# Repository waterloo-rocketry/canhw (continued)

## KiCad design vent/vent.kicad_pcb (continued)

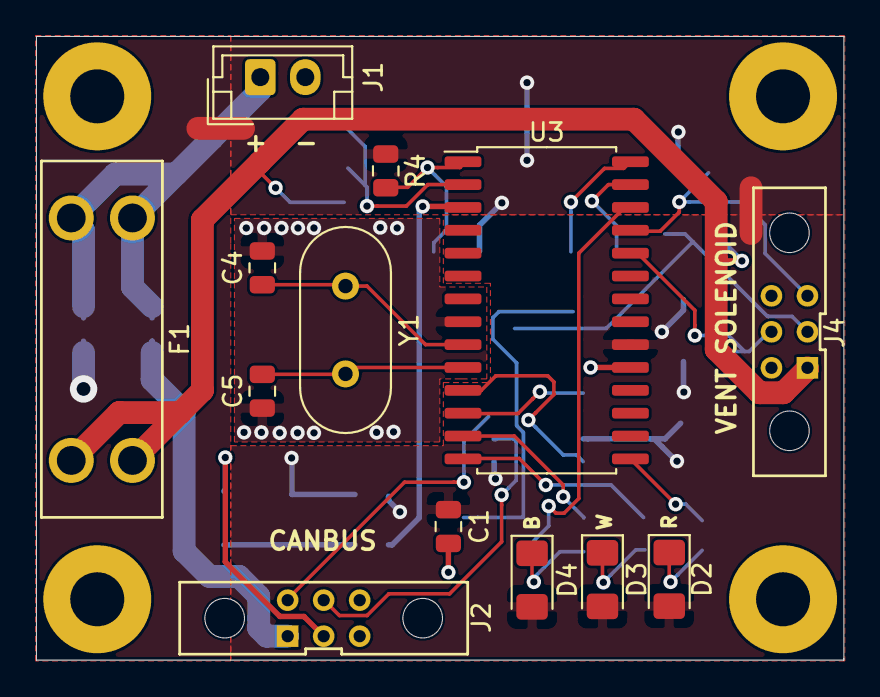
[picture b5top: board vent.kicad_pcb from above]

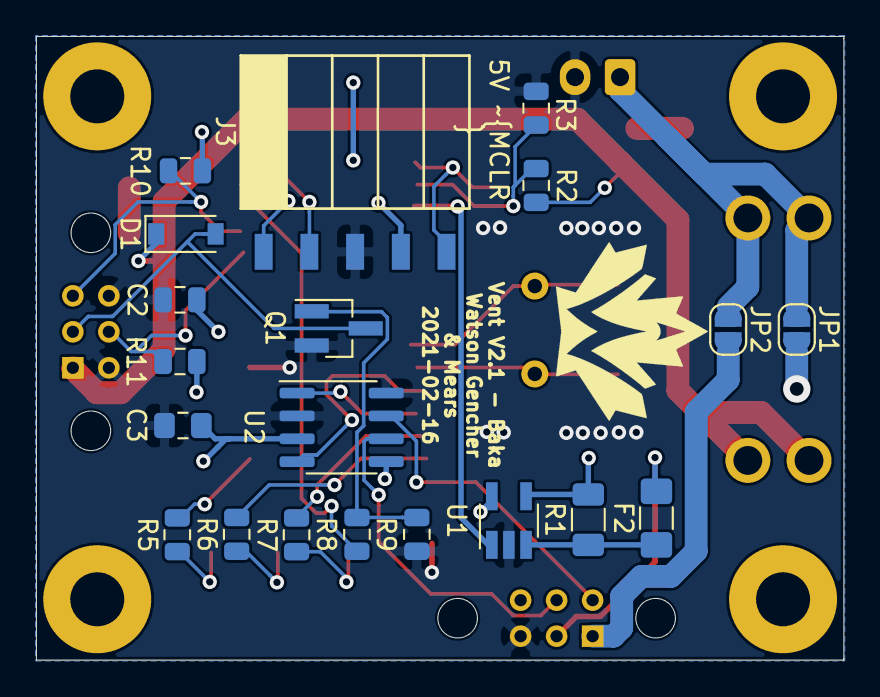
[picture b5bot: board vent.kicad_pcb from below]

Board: 2 copper layers, 44.9 x 34.6 mm, 33 parts (20 on the bottom side), 29 nets.

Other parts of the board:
JP1: +5V conn; SolderJumper-2_P1.3mm_Open_RoundedPad1.0x1.5mm
JP2: +12v conn; SolderJumper-2_P1.3mm_Open_RoundedPad1.0x1.5mm

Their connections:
+5V: JP1.1; also elsewhere on the board
+12V: JP2.1; also elsewhere on the board
unnamed 21: JP1.2, JP2.2; also elsewhere on the board

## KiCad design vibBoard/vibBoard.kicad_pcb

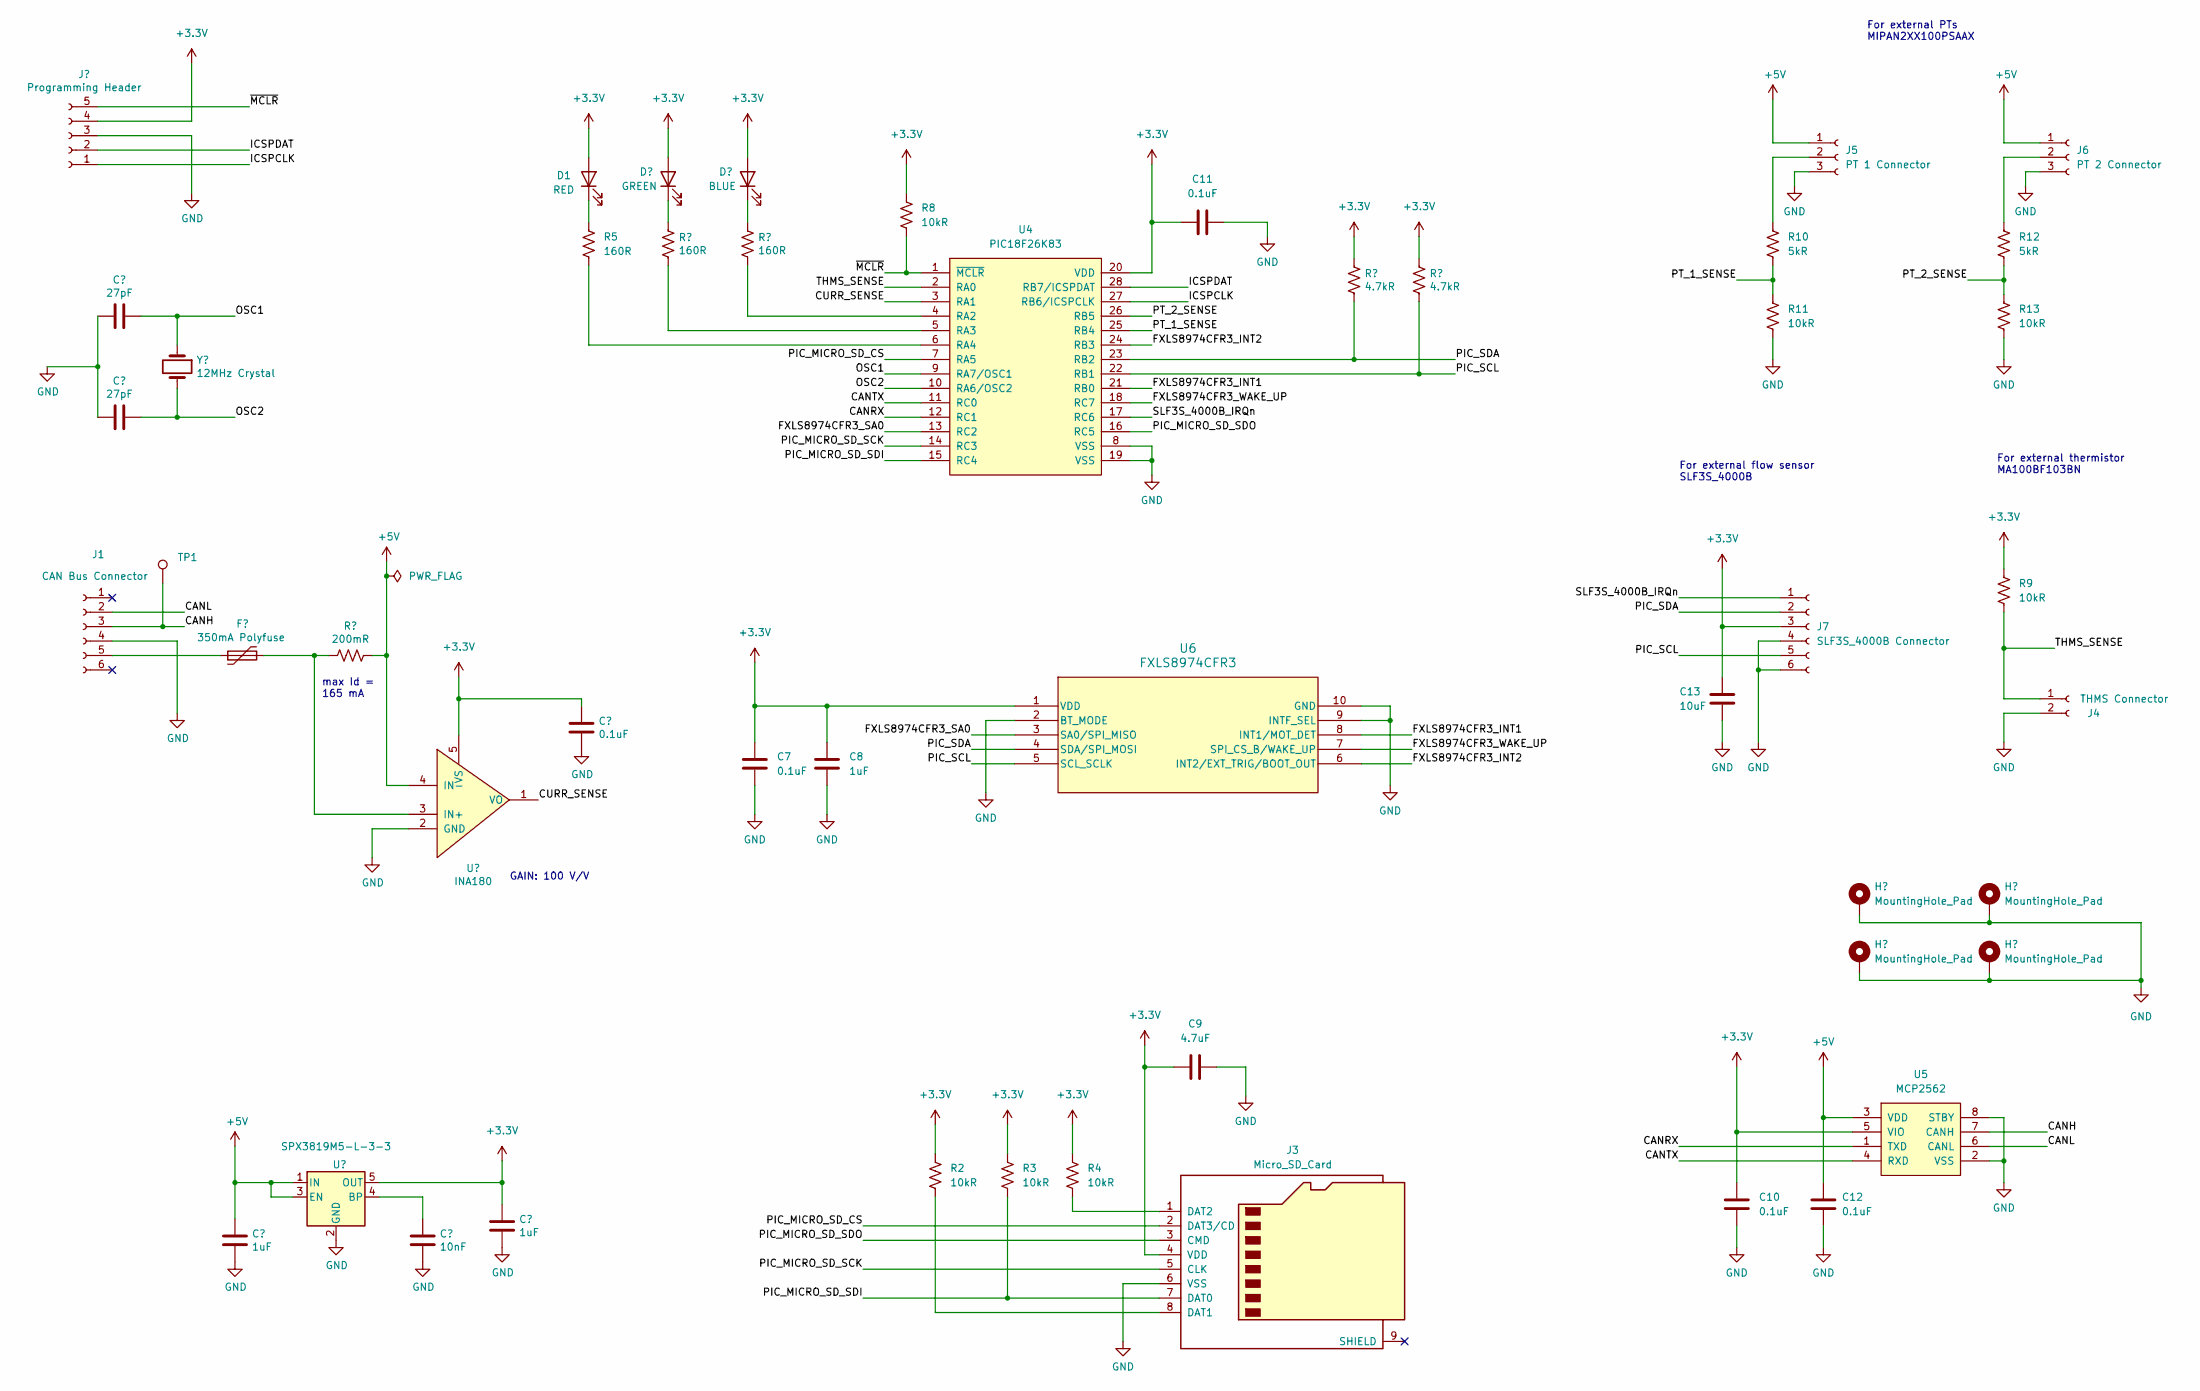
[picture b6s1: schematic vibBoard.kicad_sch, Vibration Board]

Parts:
C1, C3: 1uF; C_0805_2012Metric_Pad1.18x1.45mm_HandSolder; DigiKey 1276-6470-1-ND
C2: 10nF; C_0805_2012Metric_Pad1.18x1.45mm_HandSolder; DigiKey 732-12169-1-ND
C4, C7, C10, C11, C12: 0.1uF; C_0805_2012Metric_Pad1.18x1.45mm_HandSolder; DigiKey 311-1858-1-ND
C5, C6: 27pF; C_0805_2012Metric_Pad1.18x1.45mm_HandSolder; DigiKey 1276-2622-1-ND
C8: 1uF; C_0805_2012Metric_Pad1.18x1.45mm_HandSolder
C9: 4.7uF; C_0805_2012Metric_Pad1.18x1.45mm_HandSolder; DigiKey 1276-1244-1-ND
C13: 10uF; C_0805_2012Metric_Pad1.18x1.45mm_HandSolder
D1: RED; LED_1206_3216Metric_Pad1.42x1.75mm_HandSolder; DigiKey 160-1457-1-ND
D2: GREEN; LED_1206_3216Metric_Pad1.42x1.75mm_HandSolder; DigiKey 160-1188-1-ND
D3: BLUE; LED_1206_3216Metric_Pad1.42x1.75mm_HandSolder; DigiKey 1830-1088-1-ND
F1: 350mA Polyfuse; Fuse_1206_3216Metric_Pad1.42x1.75mm_HandSolder; DigiKey F3732CT-ND
H1, H2, H3, H4: MountingHole_Pad; MountingHole_3.2mm_M3_DIN965_Pad
J1: CAN Bus Connector; connector_Harwin_G125–MG10605M4P
J2: Programming Header; PinHeader_5x2.54_SMD_90deg_952-3198-1-ND; DigiKey 2073-BG300-05-A-L-ACT-ND
J3: Micro_SD_Card; microSD_Molex_WM6698CT-ND; DigiKey WM6698CT-ND
J4: THMS Connector; JST_PH_S2B-PH-K_1x02_P2.00mm_Horizontal
J5: PT 1 Connector; JST_PH_S3B-PH-K_1x03_P2.00mm_Horizontal
J6: PT 2 Connector; JST_PH_S3B-PH-K_1x03_P2.00mm_Horizontal
J7: SLF3S_4000B Connector; JST_PH_S6B-PH-K_1x06_P2.00mm_Horizontal
R1: 200mR; R_0805_2012Metric_Pad1.20x1.40mm_HandSolder; DigiKey WSLB-.20CT-ND
R2, R3, R4, R8, R9, R11, R13: 10kR; R_0805_2012Metric_Pad1.20x1.40mm_HandSolder; DigiKey RMCF0805FT10K0CT-ND
R5, R6, R7: 160R; R_0805_2012Metric_Pad1.20x1.40mm_HandSolder; DigiKey 738-RMCF0805FT160RCT-ND
R10, R12: 5kR; R_0805_2012Metric_Pad1.20x1.40mm_HandSolder; DigiKey RMCF0805FT10K0CT-ND
R14, R15: 4.7kR; R_0805_2012Metric_Pad1.20x1.40mm_HandSolder; DigiKey 738-RMCF0805FT160RCT-ND
TP1: TestPoint_Pad_1.0x1.0mm
U1: SPX3819M5-L-3-3; SOT-23-5; DigiKey 1016-1873-1-ND
U2: INA180; SOT-23-5_HandSoldering; DigiKey 296-INA180A3QDBVRQ1CT-ND
U4: PIC18F26K83; SOIC-28W_7.5x18.7mm_P1.27mm; DigiKey PIC18LF26K83T-I/SOCT-ND
U5: MCP2562; SOIC-8_3.9x4.9mm_P1.27mm; DigiKey MCP2562T-E/SNCT-ND
U6: FXLS8974CFR3; FXLS8974CFR3_NXP
Y1: 12MHz Crystal; Crystal_HC49-4H_Vertical; DigiKey 535-9869-1-ND

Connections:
+3.3V: C3.1, C4.1, C7.2, C8.2, C9.2, C10.2, C11.1, C13.2, D1.2 (A), D2.2 (A), D3.2 (A), J2.4, J3.4 (VDD), J7.3, R2.1, R3.1, R4.1, R8.1, R9.1, R14.1, R15.1, U1.5 (OUT), U2.5 (VS), U4.20 (VDD), U5.5 (VIO), U6.1 (VDD); also elsewhere on the board
+5V: C1.1, C12.2, J5.1, J6.1, R1.1, U1.1 (IN), U1.3 (EN), U2.4 (IN-), U5.3 (VDD); also elsewhere on the board
/CANH: J1.3, TP1.1, U5.7 (CANH)
/CANL: J1.2, U5.6 (CANL)
/CANRX: U4.12 (RC1), U5.1 (TXD)
/CANTX: U4.11 (RC0), U5.4 (RXD)
/CURR_SENSE: U2.1 (VO), U4.3 (RA1)
/FXLS8974CFR3_INT1: U4.21 (RB0), U6.8 (INT1/MOT_DET)
/FXLS8974CFR3_INT2: U4.24 (RB3), U6.6 (INT2/EXT_TRIG/BOOT_OUT)
/FXLS8974CFR3_SA0: U4.13 (RC2), U6.3 (SA0/SPI_MISO)
/FXLS8974CFR3_WAKE_UP: U4.18 (RC7), U6.7 (SPI_CS_B/WAKE_UP)
/ICSPCLK: J2.1, U4.27 (RB6/ICSPCLK)
/ICSPDAT: J2.2, U4.28 (RB7/ICSPDAT)
/OSC1: C5.1, U4.9 (RA7/OSC1), Y1.1
/OSC2: C6.1, U4.10 (RA6/OSC2), Y1.2
/PIC_MICRO_SD_CS: J3.2 (DAT3/CD), U4.7 (RA5)
/PIC_MICRO_SD_SCK: J3.5 (CLK), U4.14 (RC3)
/PIC_MICRO_SD_SDI: J3.7 (DAT0), R3.2, U4.15 (RC4)
/PIC_MICRO_SD_SDO: J3.3 (CMD), U4.16 (RC5)
/PIC_SCL: J7.5, R15.2, U4.22 (RB1), U6.5 (SCL_SCLK)
/PIC_SDA: J7.2, R14.2, U4.23 (RB2), U6.4 (SDA/SPI_MOSI)
/PT_1_SENSE: R10.2, R11.1, U4.25 (RB4)
/PT_2_SENSE: R12.2, R13.1, U4.26 (RB5)
/SLF3S_4000B_IRQn: J7.1, U4.17 (RC6)
/THMS_SENSE: J4.1, R9.2, U4.2 (RA0)
/~MCLR: J2.5, R8.2, U4.1 (~MCLR)
GND: C1.2, C2.2, C3.2, C4.2, C5.2, C6.2, C7.1, C8.1, C9.1, C10.1, C11.2, C12.1, C13.1, H1.1, H2.1, H3.1, H4.1, J1.4, J2.3, J3.6 (VSS), J4.2, J5.3, J6.3, J7.4, J7.6, R11.2, R13.2, U1.2 (GND), U2.2 (GND), U4.8 (VSS), U4.19 (VSS), U5.2 (VSS), U5.8 (STBY), U6.2 (BT_MODE), U6.9 (INTF_SEL), U6.10 (GND)
unnamed: D1.1 (K), R5.1
unnamed: D2.1 (K), R6.1
unnamed: D3.1 (K), R7.1
unnamed: F1.1, J1.5
unnamed: J3.8 (DAT1), R2.2
unnamed: J3.1 (DAT2), R4.2
unnamed: J5.2, R10.1
unnamed: J6.2, R12.1
unnamed: C2.1, U1.4 (BP)
unnamed: F1.2, R1.2, U2.3 (IN+)
unnamed: R7.2, U4.4 (RA2)
unnamed: R6.2, U4.5 (RA3)
unnamed: R5.2, U4.6 (RA4)

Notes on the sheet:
For external flow sensor SLF3S_4000B
max Id = 165 mA
GAIN: 100 V/V
For external thermistor MA100BF103BN
For external PTs MIPAN2XX100PSAAX

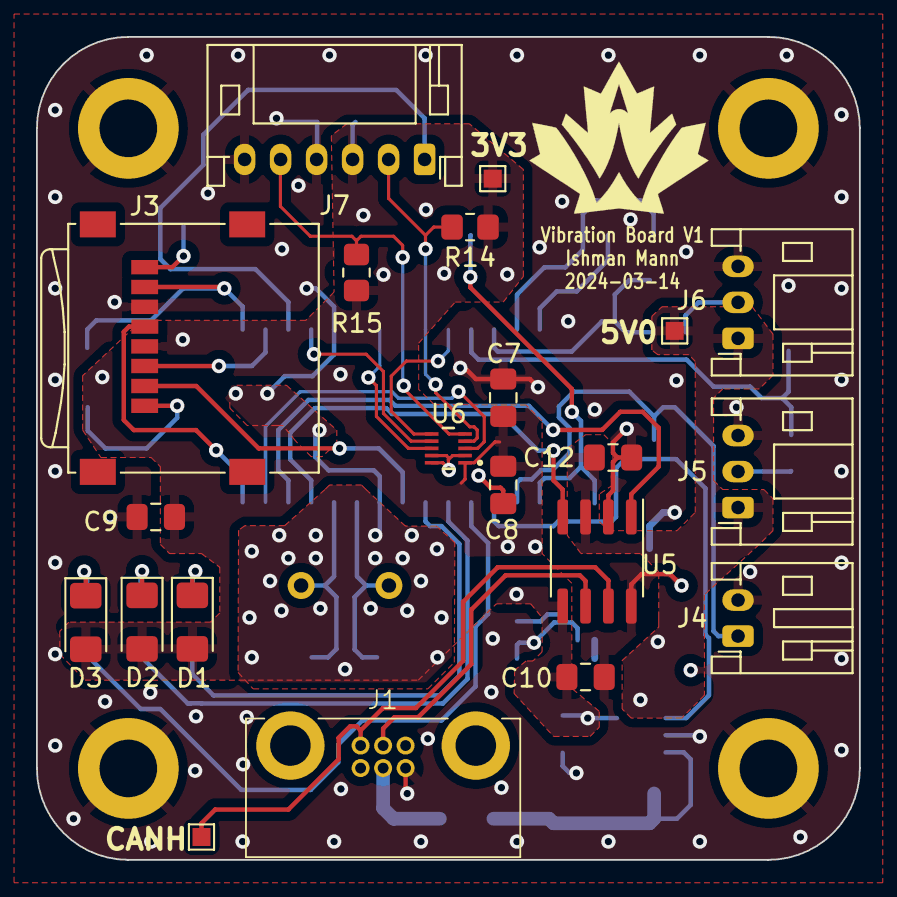
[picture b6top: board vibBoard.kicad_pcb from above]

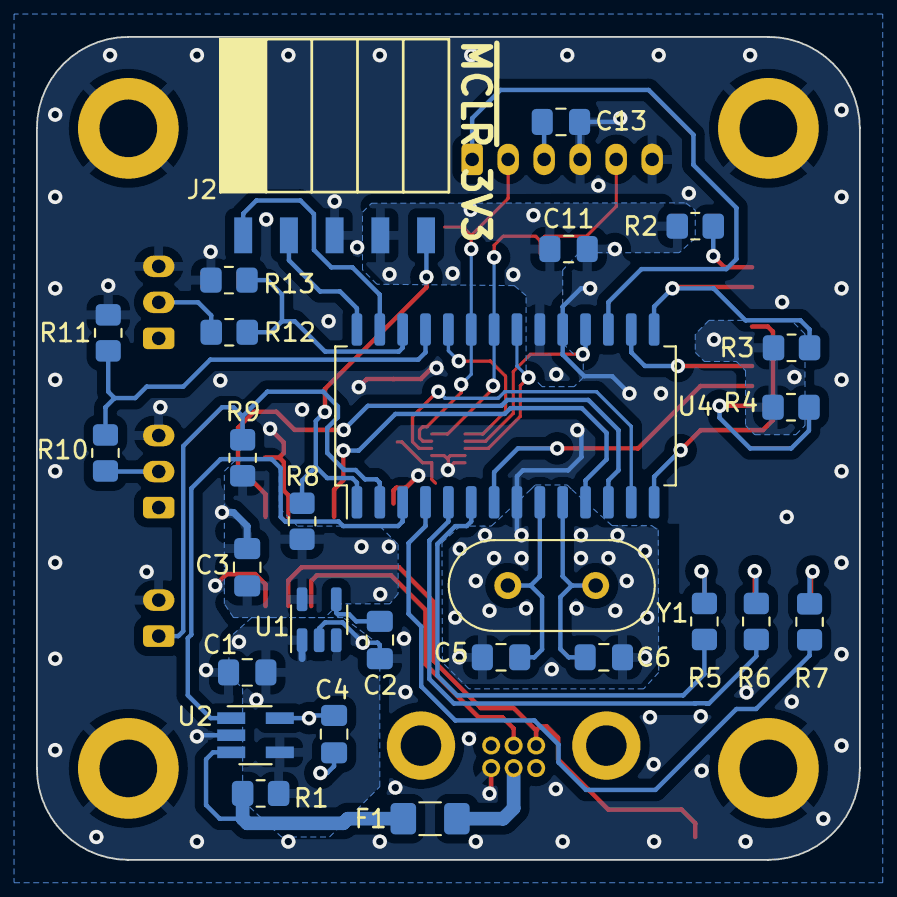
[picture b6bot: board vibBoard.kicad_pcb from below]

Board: 2 copper layers, 45.7 x 45.7 mm, 52 parts (27 on the bottom side), 40 nets.

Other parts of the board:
TP2, TP3: TestPoint_Pad_1.0x1.0mm

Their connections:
+3.3V: TP2.1; also elsewhere on the board
+5V: TP3.1; also elsewhere on the board
